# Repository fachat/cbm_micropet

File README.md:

# Micro-PET R3

Note: this is a part of a larger set of repositories, with [upet_family](https://github.com/fachat/upet_family) as the main repository.

This is a re-incarnation of the Commodore PET computer(s) from the later 1970s.

It is build on a PCB slightly larger than a Eurocard board and has only parts that can still be obtained new in 2024.
The current version is 3.0A

Here is the [Overview video](https://youtu.be/COlfqcaY7rI)

Some more videos on the build process can be found here [YT 8-bit times](https://youtube.com/playlist?list=PLi1dzy7kw1iybjcUccgjCV4fhNH4IPWSx)

## Features

The board is built with a number of features:

- Commodore 3032 / 4032 / 8032 / 8296 with options menu to select at boot
  - Boot-menu to select different PET versions to run (BASIC 1, 2, 4)
  - 40 and 80 col character display
  - 8296 memory map emulation
  - IEEE488 interface (card edge and 24pin flat ribbon cable)
  - Tape connector (card edge, 5V only)
  - PET graphics keyboard, or alternatively a C64 keyboard
- Improved system design:
  - 512k video RAM, plus 512k fast RAM, accessible using banks on the W65816 CPU
  - boot from an SPI Flash ROM
  - up to 17.5 MHz mode (via configuration register)
  - Write protection for the PET ROMs once copied to RAM
  - lower 32k RAM mappable from all of the 512k fast RAM
  - Audio output using a DAC with DMA
- Improved Video output:
  - VGA colour video output
  - up to 96x72 characters on screen
  - hires modes up to a 768x576 resolution
  - 16 out of 64 colour palette, Colour-PET or C128 VDC-compatible, Sprites
  - Hires graphics mode (using a configuration register)
  - modifyable character set
  - multiple video pages mappable to $8000 video mem address

## Overview

The system architecture is actually rather simple, as you can see in the following graphics.

The main functionality is "hidden" inside the FPGA. It does:

1. clock generation and management
2. memory mapping
3. video generation.
4. SPI interface and boot
5. DAC DMA

On the CPU side of the FPGA it is actually a rather almost normal 65816 computer, 
with the exception that the bank register (that catches and stores the address lines 
A16-23 from the CPU's data bus) is in the FPGA, and that there is no ROM. The ROM has been
replaced with some code in the FPGA that copies the initial program to the CPU accessible
RAM, taking it from the Flash Boot ROM via SPI. This actually simplifies the design,
as 

1. parallel ROMs are getting harder to come by and
2. they are typically not as fast as is needed, and
3. with the SPI boot they don't occupy valuable CPU address space.

The video generation is done using time-sharing access to the video RAM.
The VGA output is 768x576 at 60Hz. So there is a 28ns slot per pixel on the screen, 
with a pixel clock of 35MHz.

The system runs at 17.5MHz, so a byte of pixel output (i.e. eight pixels) has four
memory accesses to VRAM. Two of them are reserved for video access, one for fetching the
character data (e.g. at $08xxx in the PET), and the second one to fetch the "character ROM"
data, i.e. the pixel data for a character. This is also stored in VRAM, and is being loaded
there from the Flash Boot ROM by the initial boot loader.

The FPGA reads the character data, stores it to fetch the character pixel data, and streams
that out using its internal video shift register.

For more detailled descriptions of the features and how to use them, pls see the 
[FPGA repository](https://github.com/fachat/upet_fpga) that contains the code for the FPGA,
as described in the next section.

## Version History

- [Revision 2.1A](https://github.com/fachat/cbm_micropet/tree/r2.1a): the first one with boot-from-SPI, and card edge connectors for IEEE and tape.
- [Revision 1.1B](https://github.com/fachat/cbm_micropet/tree/r1.1b): the original one with parallel ROMs, and no SPI boot; also, no card edge connectors

## Building

Here are four subdirectories:

- [Board](Board/) that contains the board schematics and layout
- [Case](Case/) 3-D printed supports and keyboards to mount board in a C64c case

In addition, two other repositories are needed - they are separate as they are shared with other variants of the upet-family:

- [FPGA](https://github.com/fachat/upet_fpga) contains the VHDL code to program the FPGA logic chip used, and describes the configuration options - including the SPI usage, the DAC usage, and the Video features.
- [ROM](https://github.com/fachat/upet_roms) ROM contents to boot

### Board

To have the board built, you can use the gerbers that are stored in the zip file in the Board/production subdirectory.

To populate the board, there is an interactive bom (bill of materials) from KiCad, as well as the KiCad BOM CSV export in the [bom](Board/bom/) folder.
The parts I used are in the [Mouser BOM](Board/micropet_v3.0a-BOM.xlsx).

The BOM contains an Ethernet breakout board that is put into the connectors "above" the USB port. As an alternative you could use the 
[Wifi breakout board](https://github.com/fachat/upet_wifi). Note that at this time, this is not tested / programmed yet.

### FPGA

The FPGA is a Xilinx Spartan 6 programmable logic chip. It runs on 3.3V and it is programmed in VHDL.

To build the FPGA content, clone the [FPGA](https://github.com/fachat/upet_fpga) repository, and look for the ShellUPet.bin.
This needs to be programmed into the SPI flash chip containing the configration for the FPGA.

### ROM

To build the boot ROM image, clone the [ROM](https://github.com/fachat/upet_roms) repository, and build the spiimg70m file. This needs to be 
programmed into the SPI flash ROM containing the 65816 boot code.

The ROM image can be built using gcc, xa65, and make. Use your favourite EPROM programmer to burn it into the SPI Flash chip.

The ROM contains images of all required ROM images for BASIC 1, 2, and 4, and corresponding editor ROMs, including
some that have been extended with wedges.

The updated editor ROMs are from [Steve's Editor ROM project](http://www.6502.org/users/sjgray/projects/editrom/index.html) and can handle C64 keyboards, has a DOS wedge included, and resets into the Micro-PET boot menu.
For more details see the description in the ROM repository.

### Case

The [Case](Case/) subdirectory holds some supporting 3D models, to use an existing C64-II case for the Micro-PET. 

Also, it contains the models for custom key caps for a PET N-type keyboard, as is default for the Micro-PET. 
As keyboard PCB I suggest using Steve Gray's [PET keyboard replacements](http://cbmsteve.ca/mxkeyboards/index.html) using modern, MX-type key switches.

## Gallery (Still R2)

Note: the published schematics and board has the extra wires fixed/included.

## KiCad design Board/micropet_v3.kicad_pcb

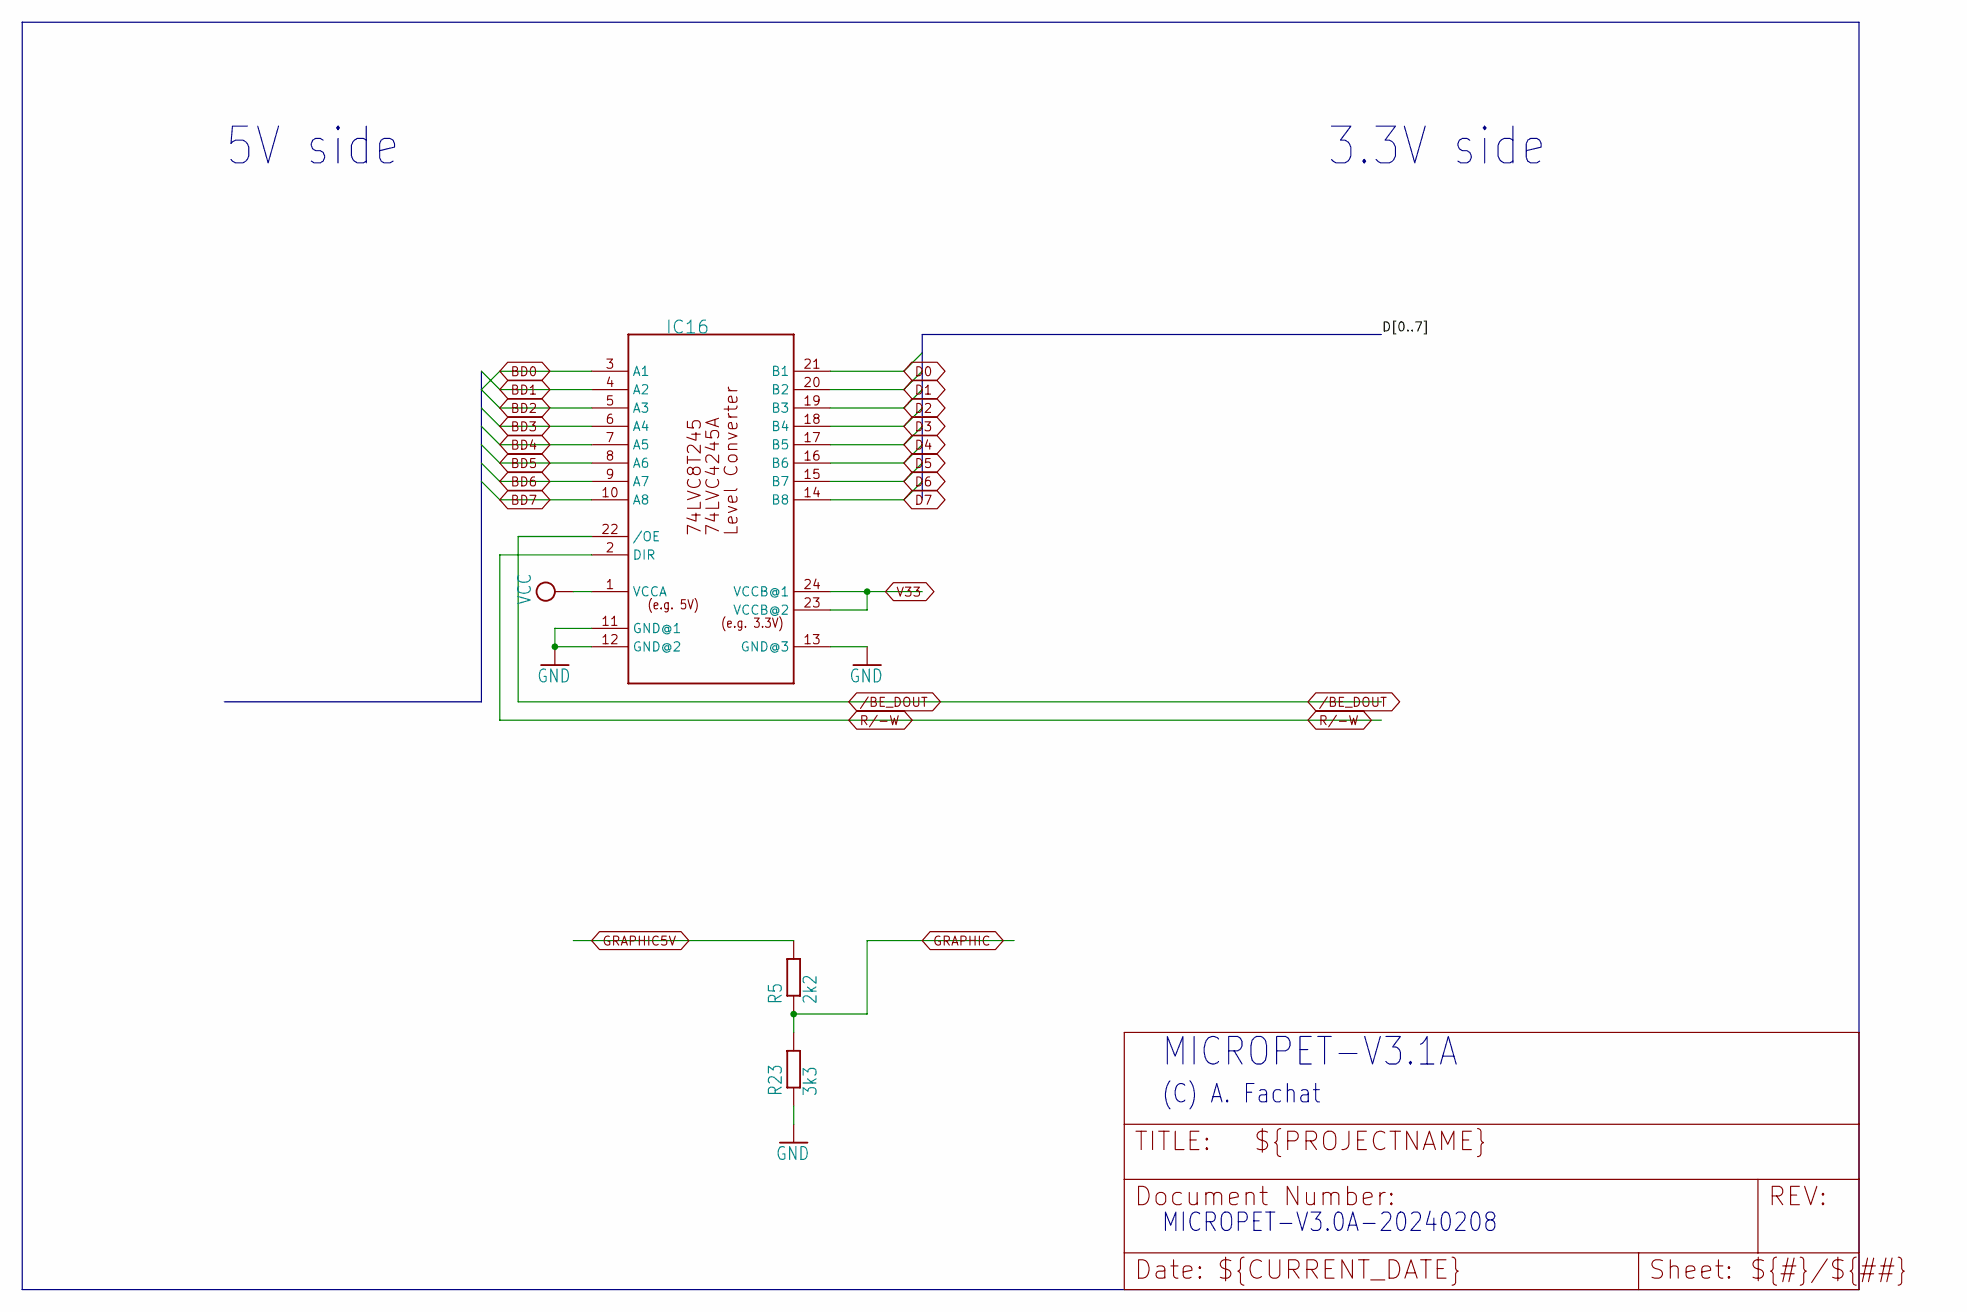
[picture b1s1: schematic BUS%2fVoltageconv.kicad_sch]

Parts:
IC16: 74LVC8T245SO24; SO24L
R5: 2k2; 0204_5
R23: 3k3; 0204_5

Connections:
BD0: IC16.3 (A1); also elsewhere on the board
BD1: IC16.4 (A2); also elsewhere on the board
BD2: IC16.5 (A3); also elsewhere on the board
BD3: IC16.6 (A4); also elsewhere on the board
BD4: IC16.7 (A5); also elsewhere on the board
BD5: IC16.8 (A6); also elsewhere on the board
BD6: IC16.9 (A7); also elsewhere on the board
BD7: IC16.10 (A8); also elsewhere on the board
D0: IC16.21 (B1); also elsewhere on the board
D1: IC16.20 (B2); also elsewhere on the board
D2: IC16.19 (B3); also elsewhere on the board
D3: IC16.18 (B4); also elsewhere on the board
D4: IC16.17 (B5); also elsewhere on the board
D5: IC16.16 (B6); also elsewhere on the board
D6: IC16.15 (B7); also elsewhere on the board
D7: IC16.14 (B8); also elsewhere on the board
GND: IC16.11 (GND@1), IC16.12 (GND@2), IC16.13 (GND@3), R23.1; also elsewhere on the board
GRAPHIC: R5.1, R23.2; also elsewhere on the board
GRAPHIC5V: R5.2; also elsewhere on the board
V33: IC16.23 (VCCB@2), IC16.24 (VCCB@1); also elsewhere on the board
VCC: IC16.1 (VCCA); also elsewhere on the board
/BE_DOUT: IC16.22 (/OE); also elsewhere on the board

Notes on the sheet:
3.3V side
MICROPET-V3.1A
(C) A. Fachat
5V side
MICROPET-V3.0A-20240208

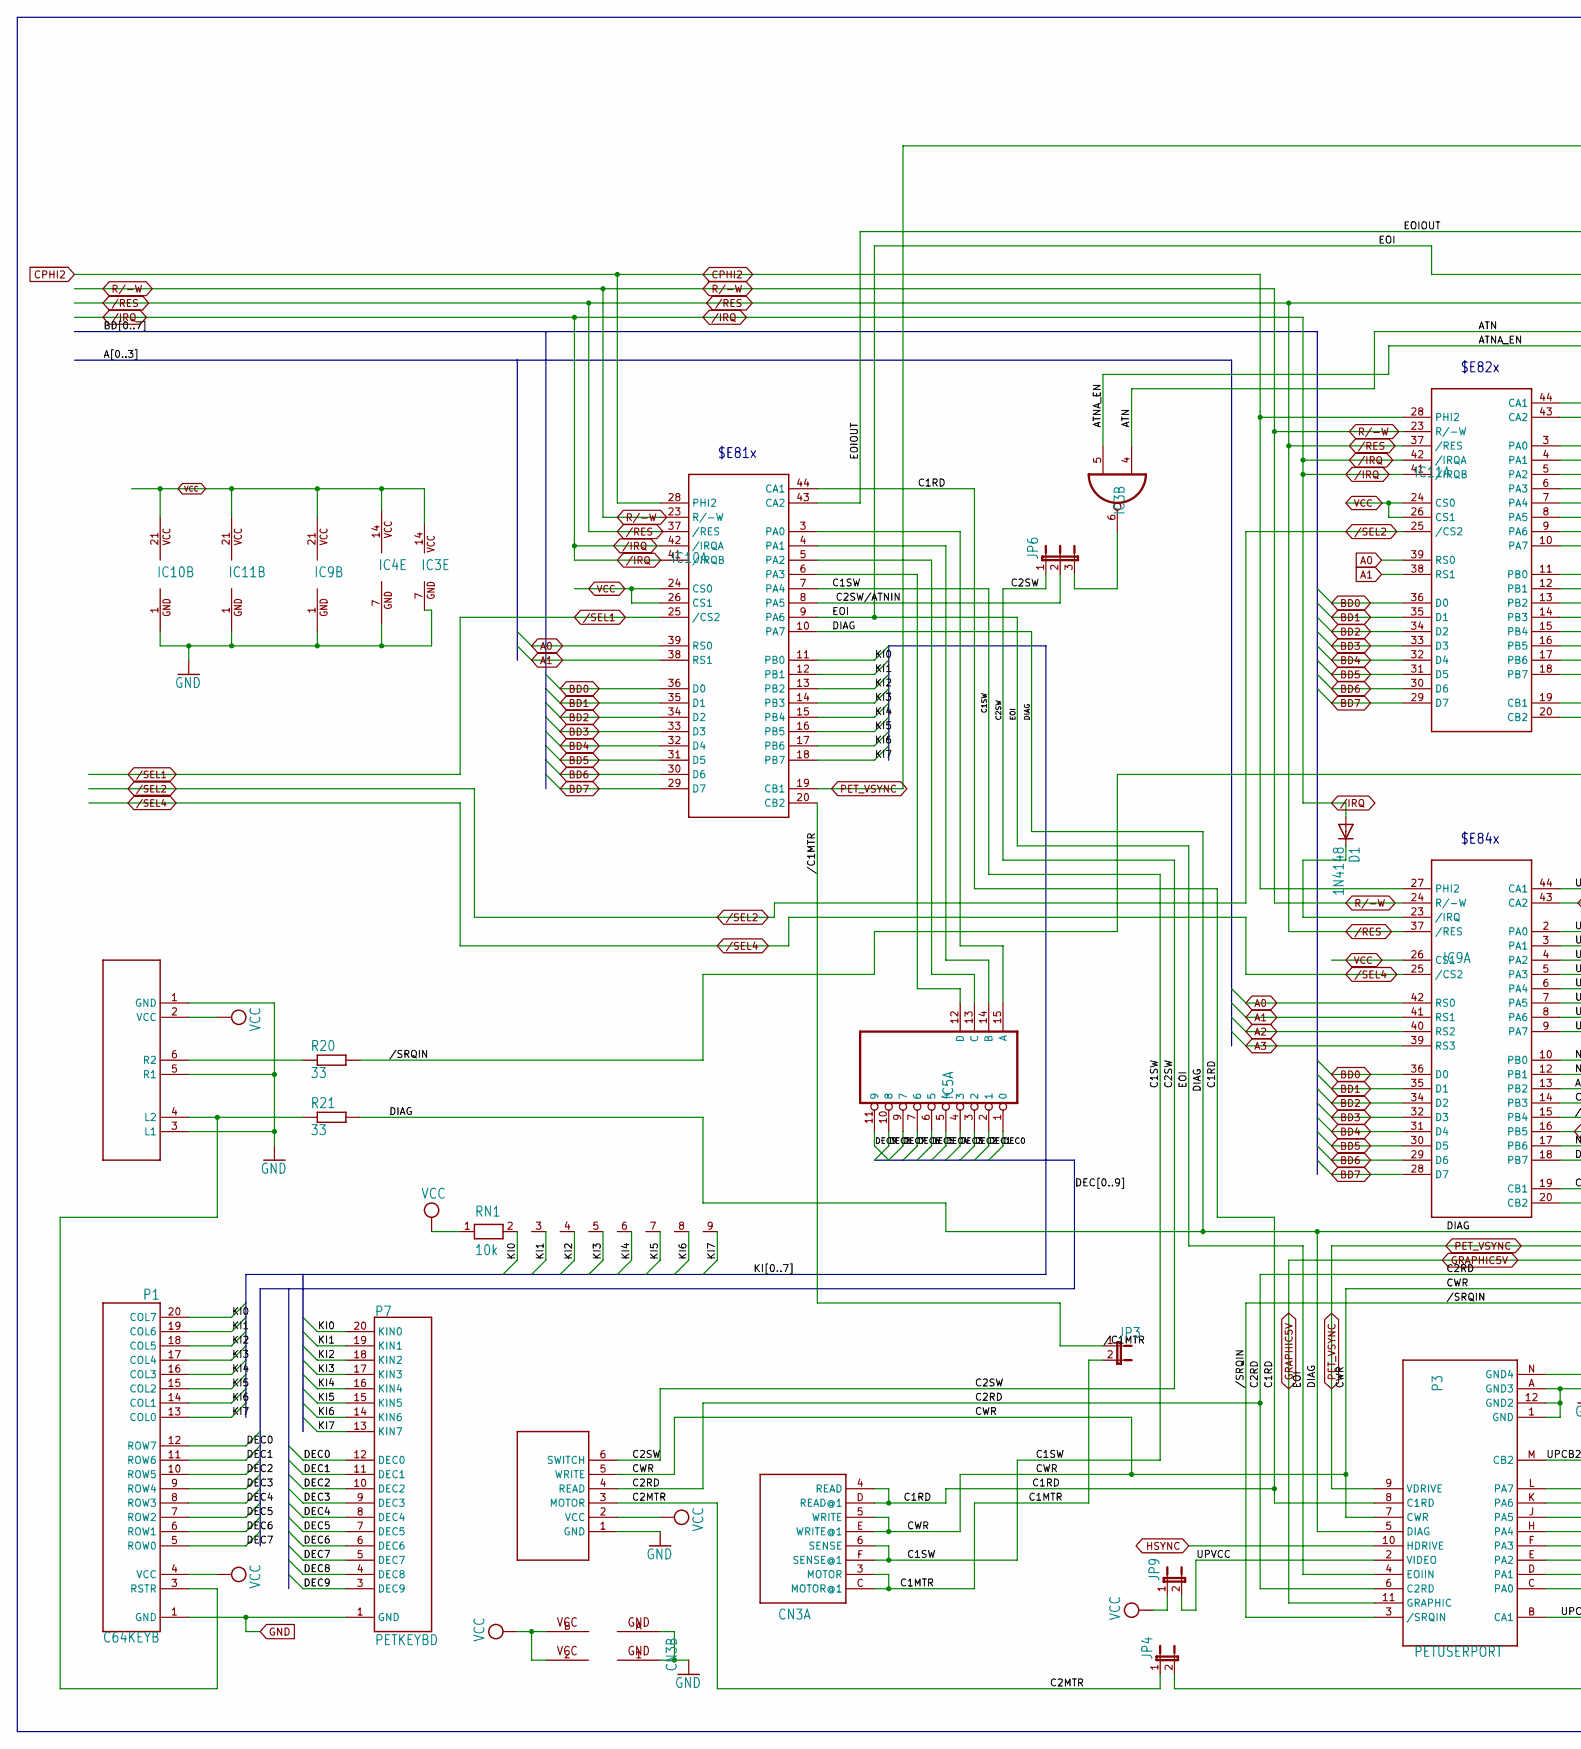
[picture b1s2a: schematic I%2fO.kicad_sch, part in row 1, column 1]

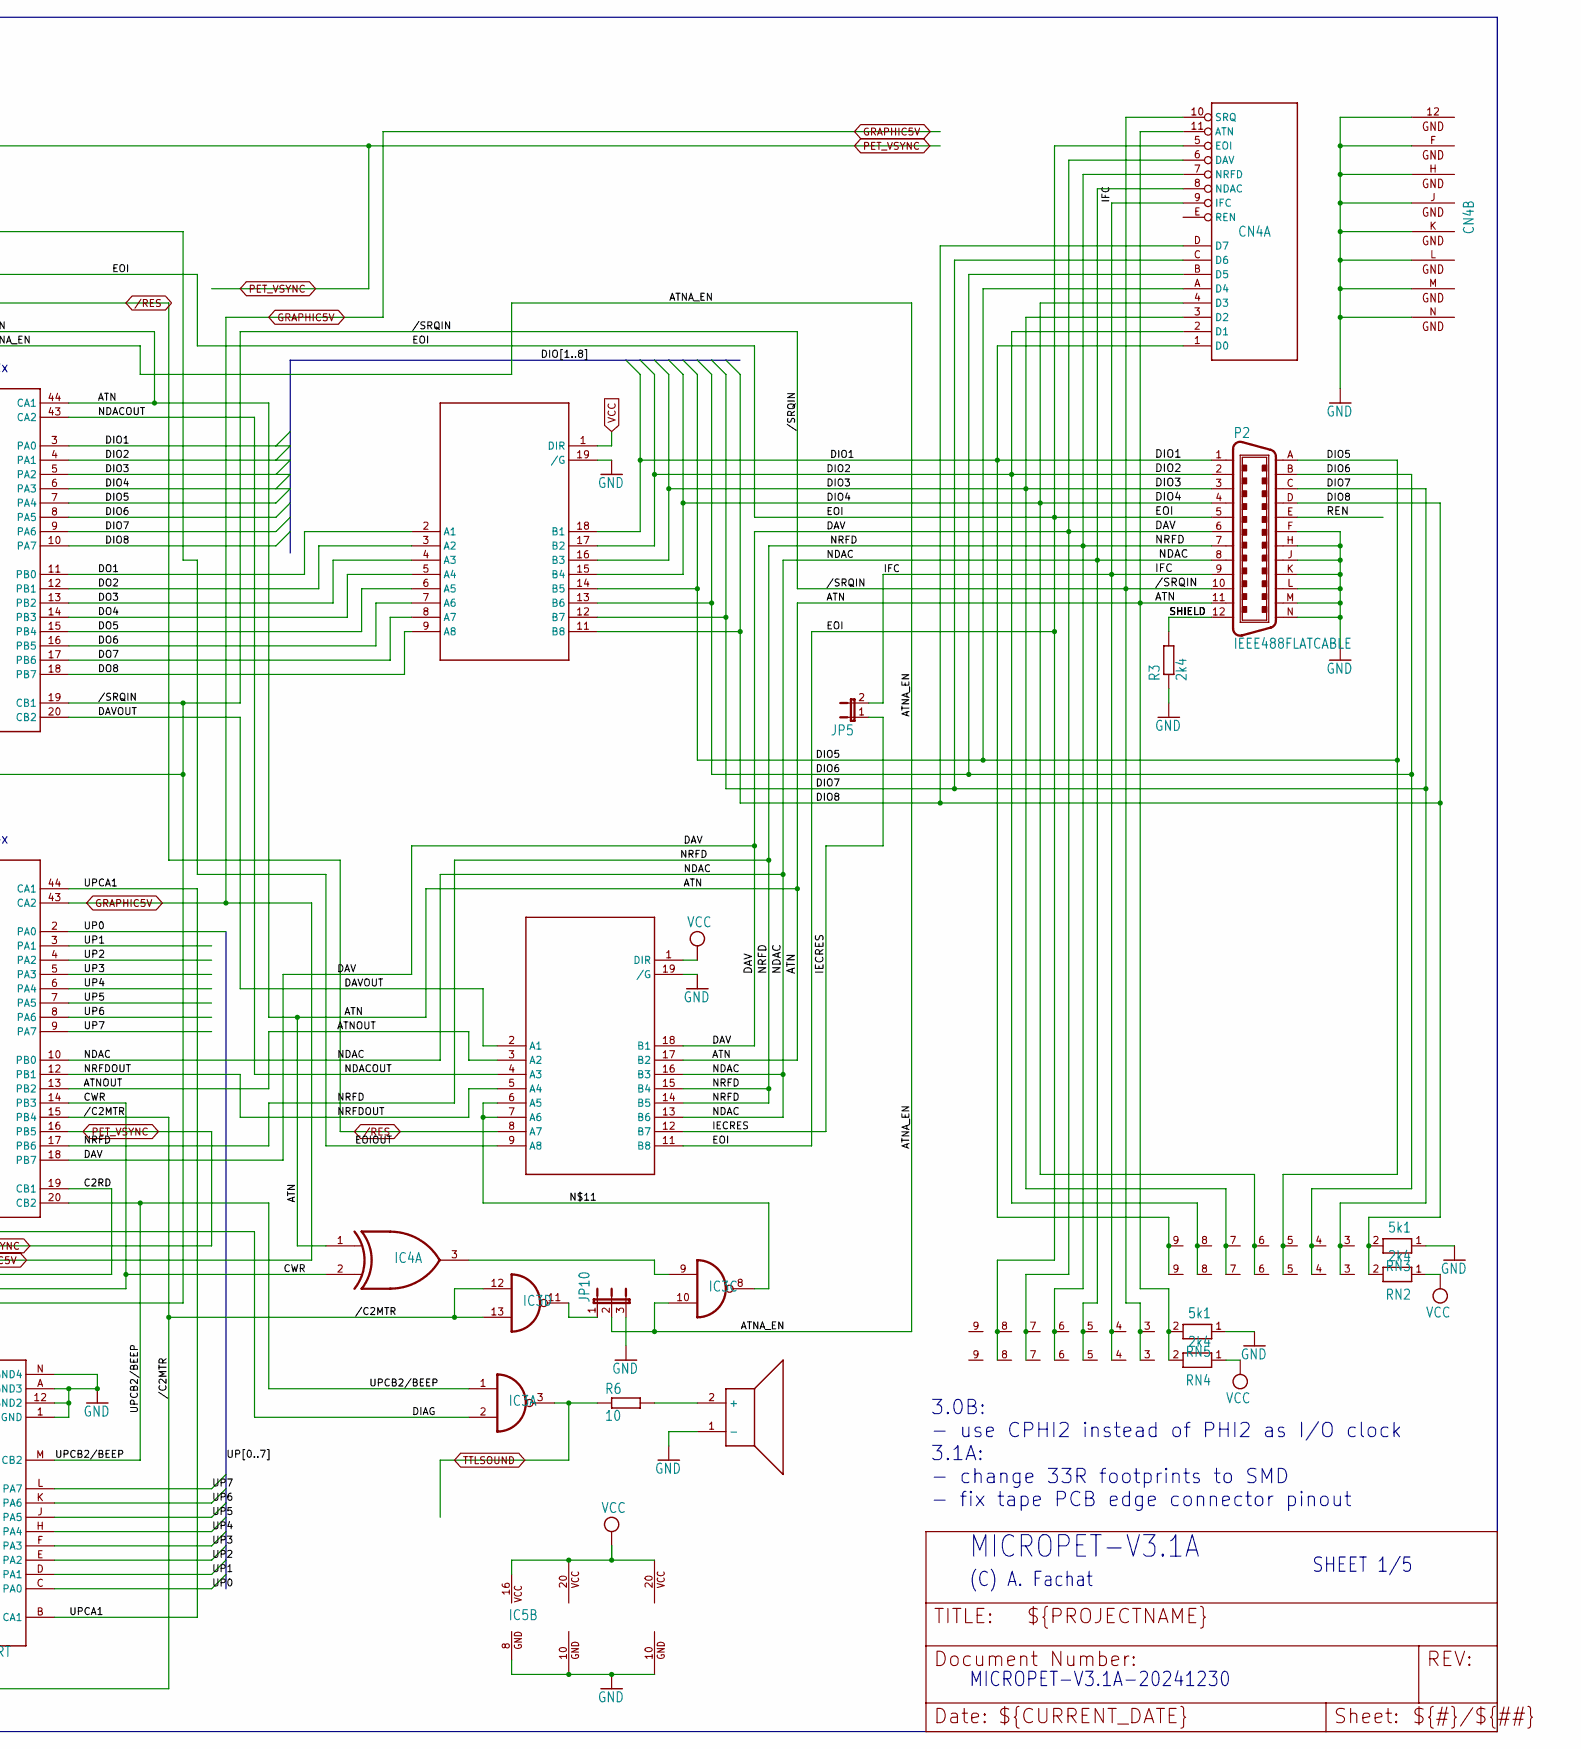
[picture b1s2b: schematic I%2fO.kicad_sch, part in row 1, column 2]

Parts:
BEEP1: PIEZOBEEPER; JP2
CN3: PORT_CASSETTE_EDGE; MA156_6-2_KEYED
CN4: PORT_IEEE_EDGE; MA156_12-2_IEEE
D1: 1N4148; D-5
IC3: 7400D; SO14
IC4: 7486D; SO14
IC5: 74145N; DIL16
IC9: VIAPLCC; PLCC44
IC10, IC11: PIAPLCC; PLCC44
JP3, JP4, JP5, JP9: JP1E; JP1
JP6, JP10: JP2E; JP2
P1: C64KEYB
P2: IEEE488FLATCABLE; FLAT24
P3: PETUSERPORT; FLAT24
P6: CBMTAPE; JP6
P7: PETKEYBD; C64KEYB
R3: 2k4; 0207_2V
R6: 10; 0207_2V
R20, R21: 33; R_0805_2012Metric_Pad1.20x1.40mm_HandSolder
RN1: 10k; RN-9
RN2, RN4: 2k4; RN-9
RN3, RN5: 5k1; RN-9
U$5, U$6: 74LS641; DIL20
U$11: PETSKEY_EXTRA; JP6

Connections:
/I/O/ATN: CN4.11 (ATN), IC3.4 (I0), IC4.1 (I0), IC11.44 (CA1), P2.11, RN4.2, RN5.2, U$6.17 (B2)
/I/O/ATNA_EN: IC3.5 (I1), IC3.10 (I1), JP10.2
/I/O/ATNOUT: IC9.13 (PB2), U$6.3 (A2)
/I/O/C1MTR: CN3.3 (MOTOR), CN3.C (MOTOR@1), JP3.2
/I/O/C1RD: CN3.4 (READ), CN3.D (READ@1), IC10.44 (CA1), P3.8 (C1RD)
/I/O/C1SW: CN3.6 (SENSE), CN3.F (SENSE@1), IC10.7 (PA4)
/I/O/C2MTR: JP4.1, P6.3 (MOTOR)
/I/O/C2RD: IC9.19 (CB1), P3.6 (C2RD), P6.4 (READ)
/I/O/C2SW: JP6.1, P6.6 (SWITCH)
/I/O/C2SW/ATNIN: IC10.8 (PA5), JP6.2
/I/O/CWR: CN3.5 (WRITE), CN3.E (WRITE@1), IC4.2 (I1), IC9.14 (PB3), P3.7 (CWR), P6.5 (WRITE)
/I/O/DAV: CN4.6 (DAV), IC9.18 (PB7), P2.6, RN4.7, RN5.7, U$6.18 (B1)
/I/O/DAVOUT: IC11.20 (CB2), U$6.2 (A1)
/I/O/DEC0: IC5.1 (0), P1.12 (ROW7), P7.12 (DEC0)
/I/O/DEC1: IC5.2 (1), P1.11 (ROW6), P7.11 (DEC1)
/I/O/DEC2: IC5.3 (2), P1.10 (ROW5), P7.10 (DEC2)
/I/O/DEC3: IC5.4 (3), P1.9 (ROW4), P7.9 (DEC3)
/I/O/DEC4: IC5.5 (4), P1.8 (ROW3), P7.8 (DEC4)
/I/O/DEC5: IC5.6 (5), P1.7 (ROW2), P7.7 (DEC5)
/I/O/DEC6: IC5.7 (6), P1.6 (ROW1), P7.6 (DEC6)
/I/O/DEC7: IC5.9 (7), P1.5 (ROW0), P7.5 (DEC7)
/I/O/DEC8: IC5.10 (8), P7.4 (DEC8)
/I/O/DEC9: IC5.11 (9), P7.3 (DEC9)
/I/O/DIAG: IC3.2 (I1), IC10.10 (PA7), P3.5 (DIAG), R21.2
/I/O/DIO1: CN4.1 (D0), IC11.3 (PA0), P2.1, RN2.9, RN3.9, U$5.18 (B1)
/I/O/DIO2: CN4.2 (D1), IC11.4 (PA1), P2.2, RN2.8, RN3.8, U$5.17 (B2)
/I/O/DIO3: CN4.3 (D2), IC11.5 (PA2), P2.3, RN2.7, RN3.7, U$5.16 (B3)
/I/O/DIO4: CN4.4 (D3), IC11.6 (PA3), P2.4, RN2.6, RN3.6, U$5.15 (B4)
/I/O/DIO5: CN4.A (D4), IC11.7 (PA4), P2.A (13), RN2.5, RN3.5, U$5.14 (B5)
/I/O/DIO6: CN4.B (D5), IC11.8 (PA5), P2.B (14), RN2.4, RN3.4, U$5.13 (B6)
/I/O/DIO7: CN4.C (D6), IC11.9 (PA6), P2.C (15), RN2.3, RN3.3, U$5.12 (B7)
/I/O/DIO8: CN4.D (D7), IC11.10 (PA7), P2.D (16), RN2.2, RN3.2, U$5.11 (B8)
/I/O/DO1: IC11.11 (PB0), U$5.2 (A1)
/I/O/DO2: IC11.12 (PB1), U$5.3 (A2)
/I/O/DO3: IC11.13 (PB2), U$5.4 (A3)
/I/O/DO4: IC11.14 (PB3), U$5.5 (A4)
/I/O/DO5: IC11.15 (PB4), U$5.6 (A5)
/I/O/DO6: IC11.16 (PB5), U$5.7 (A6)
/I/O/DO7: IC11.17 (PB6), U$5.8 (A7)
/I/O/DO8: IC11.18 (PB7), U$5.9 (A8)
/I/O/EOI: CN4.5 (EOI), IC10.9 (PA6), P2.5, P3.4 (EOIIN), RN4.8, RN5.8, U$6.11 (B8)
/I/O/EOIOUT: IC10.43 (CA2), U$6.9 (A8)
/I/O/IECRES: JP5.1, U$6.12 (B7)
/I/O/IFC: CN4.9 (IFC), JP5.2, P2.9, RN4.4, RN5.4
/I/O/KI0: IC10.11 (PB0), P1.20 (COL7), P7.20 (KIN0), RN1.2
/I/O/KI1: IC10.12 (PB1), P1.19 (COL6), P7.19 (KIN1), RN1.3
/I/O/KI2: IC10.13 (PB2), P1.18 (COL5), P7.18 (KIN2), RN1.4
/I/O/KI3: IC10.14 (PB3), P1.17 (COL4), P7.17 (KIN3), RN1.5
/I/O/KI4: IC10.15 (PB4), P1.16 (COL3), P7.16 (KIN4), RN1.6
/I/O/KI5: IC10.16 (PB5), P1.15 (COL2), P7.15 (KIN5), RN1.7
/I/O/KI6: IC10.17 (PB6), P1.14 (COL1), P7.14 (KIN6), RN1.8
/I/O/KI7: IC10.18 (PB7), P1.13 (COL0), P7.13 (KIN7), RN1.9
/I/O/N$11: IC3.8 (O), U$6.6 (A5), U$6.7 (A6)
/I/O/NDAC: CN4.8 (NDAC), IC9.10 (PB0), P2.8, RN4.5, RN5.5, U$6.13 (B6), U$6.16 (B3)
/I/O/NDACOUT: IC11.43 (CA2), U$6.4 (A3)
/I/O/NRFD: CN4.7 (NRFD), IC9.17 (PB6), P2.7, RN4.6, RN5.6, U$6.14 (B5), U$6.15 (B4)
/I/O/NRFDOUT: IC9.12 (PB1), U$6.5 (A4)
/I/O/REN: P2.E (17)
/I/O/SHIELD: P2.12, R3.2
/I/O/UP0: IC9.2 (PA0), P3.C (PA0)
/I/O/UP1: IC9.3 (PA1), P3.D (PA1)
/I/O/UP2: IC9.4 (PA2), P3.E (PA2)
/I/O/UP3: IC9.5 (PA3), P3.F (PA3)
/I/O/UP4: IC9.6 (PA4), P3.H (PA4)
/I/O/UP5: IC9.7 (PA5), P3.J (PA5)
/I/O/UP6: IC9.8 (PA6), P3.K (PA6)
/I/O/UP7: IC9.9 (PA7), P3.L (PA7)
/I/O/UPCA1: IC9.44 (CA1), P3.B (CA1)
/I/O/UPCB2/BEEP: IC3.1 (I0), IC9.20 (CB2), P3.M (CB2)
/I/O/UPVCC: JP9.2, P3.2 (VIDEO)
/I/O//C1MTR: IC10.20 (CB2), JP3.1
/I/O//C2MTR: IC3.12 (I0), IC3.13 (I1), IC9.15 (PB4), JP4.2
/I/O//SRQIN: CN4.10 (SRQ), IC11.19 (CB1), P2.10, P3.3 (/SRQIN), R20.2, RN4.3, RN5.3
A0: IC9.42 (RS0), IC10.39 (RS0), IC11.39 (RS0); also elsewhere on the board
A1: IC9.41 (RS1), IC10.38 (RS1), IC11.38 (RS1); also elsewhere on the board
A2: IC9.40 (RS2); also elsewhere on the board
A3: IC9.39 (RS3); also elsewhere on the board
BD0: IC9.36 (D0), IC10.36 (D0), IC11.36 (D0); also elsewhere on the board
BD1: IC9.35 (D1), IC10.35 (D1), IC11.35 (D1); also elsewhere on the board
BD2: IC9.34 (D2), IC10.34 (D2), IC11.34 (D2); also elsewhere on the board
BD3: IC9.32 (D3), IC10.33 (D3), IC11.33 (D3); also elsewhere on the board
BD4: IC9.31 (D4), IC10.32 (D4), IC11.32 (D4); also elsewhere on the board
BD5: IC9.30 (D5), IC10.31 (D5), IC11.31 (D5); also elsewhere on the board
BD6: IC9.29 (D6), IC10.30 (D6), IC11.30 (D6); also elsewhere on the board
BD7: IC9.28 (D7), IC10.29 (D7), IC11.29 (D7); also elsewhere on the board
CPHI2: IC9.27 (PHI2), IC10.28 (PHI2), IC11.28 (PHI2); also elsewhere on the board
GND: BEEP1.1 (-), CN3.1 (GND), CN3.A (GND@1), CN4.12 (GND), CN4.F (GND@1), CN4.H (GND@2), CN4.J (GND@3), CN4.K (GND@4), CN4.L (GND@5), CN4.M (GND@6), CN4.N (GND@7), IC3.7 (GND), IC4.7 (GND), IC5.8 (GND), IC9.1 (GND), IC10.1 (GND), IC11.1 (GND), JP10.3, P1.1 (GND), P2.F (18), P2.H (19), P2.J (20), P2.K (21), P2.L (22), P2.M (23), P2.N (24), P3.1 (GND), P3.12 (GND2), P3.A (GND3), P3.N (GND4), P6.1 (GND), P7.1 (GND), R3.1, RN3.1, RN5.1, U$5.10 (GND), U$5.19 (/G), U$6.10 (GND), U$6.19 (/G), U$11.1 (GND), U$11.3 (L1), U$11.5 (R1); also elsewhere on the board
GRAPHIC5V: IC9.43 (CA2), P3.11 (GRAPHIC); also elsewhere on the board
HSYNC: P3.10 (HDRIVE); also elsewhere on the board
unnamed: BEEP1.2 (+), R6.2
unnamed: IC3.6 (O), JP6.3
unnamed: IC3.9 (I0), IC4.3 (O)
unnamed: IC3.11 (O), JP10.1
unnamed: D1.C, IC9.23 (/IRQ)
unnamed: IC5.15 (A), IC10.3 (PA0)
unnamed: IC5.14 (B), IC10.4 (PA1)
unnamed: IC5.13 (C), IC10.5 (PA2)
unnamed: IC5.12 (D), IC10.6 (PA3)
unnamed: P1.3 (RSTR), R21.1, U$11.4 (L2)
unnamed: R20.1, U$11.6 (R2)
PET_VSYNC: IC9.16 (PB5), IC10.19 (CB1), P3.9 (VDRIVE); also elsewhere on the board
TTLSOUND: IC3.3 (O), R6.1; also elsewhere on the board
VCC: CN3.2 (VCC), CN3.B (VCC@1), IC3.14 (VCC), IC4.14 (VCC), IC5.16 (VCC), IC9.21 (VCC), IC9.26 (CS1), IC10.21 (VCC), IC10.24 (CS0), IC10.26 (CS1), IC11.21 (VCC), IC11.24 (CS0), IC11.26 (CS1), JP9.1, P1.4 (VCC), P6.2 (VCC), RN1.1, RN2.1, RN4.1, U$5.1 (DIR), U$5.20 (VCC), U$6.1 (DIR), U$6.20 (VCC), U$11.2 (VCC); also elsewhere on the board
/IRQ: D1.A, IC10.41 (/IRQB), IC10.42 (/IRQA), IC11.41 (/IRQB), IC11.42 (/IRQA); also elsewhere on the board
/SEL1: IC10.25 (/CS2); also elsewhere on the board
/SEL2: IC11.25 (/CS2); also elsewhere on the board
/SEL4: IC9.25 (/CS2); also elsewhere on the board

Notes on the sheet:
$E84x
$E82x
MICROPET-V3.1A
MICROPET-V3.1A-20241230
(C) A. Fachat
$E81x
3.0B: - use CPHI2 instead of PHI2 as I/O clock 3.1A: - change 33R footprints to SMD - fix tape PCB edge connector pinout
SHEET 1/5

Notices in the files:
Board/micropet_v3.kicad_pcb:
(C) 2024
(C) 2025
